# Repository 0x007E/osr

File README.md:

# `OSR` - Output Shift Register Development Board

The `OSR` is a board with an [HEF4094B](#additional-information) or any other compatible shift-register that meets the pin requirements. The board itself can be driven from `5` to `15V`. The board offers the possibility to shift serial signals to a parallel output clocked by buttons or an external signal from any other logic board.

| Experience  | Level                                                                               |
|:------------|:-----------------------------------------------------------------------------------:|
| Soldering   |  |

# Downloads

| Type      | File                                                                                                                                                 | Description     |
|:---------:|:----------------------------------------------------------------------------------------------------------------------------------------------------:|:----------------|
| Schematic | [pdf](https://github.com/0x007E/osr/releases/latest/download/schematic.pdf) / [cadlab](https://cadlab.io/project/30669/main/files)                   | Schematic files |
| Board     | [pdf](https://github.com/0x007E/osr/releases/latest/download/pcb.pdf) / [cadlab](https://cadlab.io/project/30669/main/files)                         | Board file      |
| Drill     | [pdf](https://github.com/0x007E/osr/releases/latest/download/drill.pdf)                                                                              | Drill file      |
| BoM | [xlsx](https://github.com/0x007E/osr/releases/latest/download/bom.xlsx) / [html](https://github.com/0x007E/osr/releases/latest/download/bom.html)          | Bill of Material as Excel/interactive HTML |
| PCB    | [zip](https://github.com/0x007E/osr/releases/latest/download/kicad.zip) / [tar](https://github.com/0x007E/osr/releases/latest/download/kicad.tar.gz)    | KiCAD/Gerber/BoM/Drill files       |
| Mechanical | [zip](https://github.com/0x007E/osr/releases/latest/download/freecad.zip) / [tar](https://github.com/0x007E/osr/releases/latest/download/freecad.tar.gz) | FreeCAD/Housing and PCB (STEP/STL) files     |

# Hardware

The pcb is created with `KiCAD`. All files are built with `github actions` so that they are ready for a production environment.

## PCB

The circuit board is populated on both sides (Top, Bottom). The best way for soldering the `SMD` components is within a vapor phase soldering system and for the `THT` components with a standard soldering system.

### Top Layer

### Bottom Layer

# Additional Information

| Type       | Link                                                                 | Description                      |
|:----------:|:--------------------------------------------------------------------:|:---------------------------------|
| HEF4094B   | [pdf](https://assets.nexperia.com/documents/data-sheet/HEF4094B.pdf) | 8-stage shift-and-store register |

---

R. GAECHTER

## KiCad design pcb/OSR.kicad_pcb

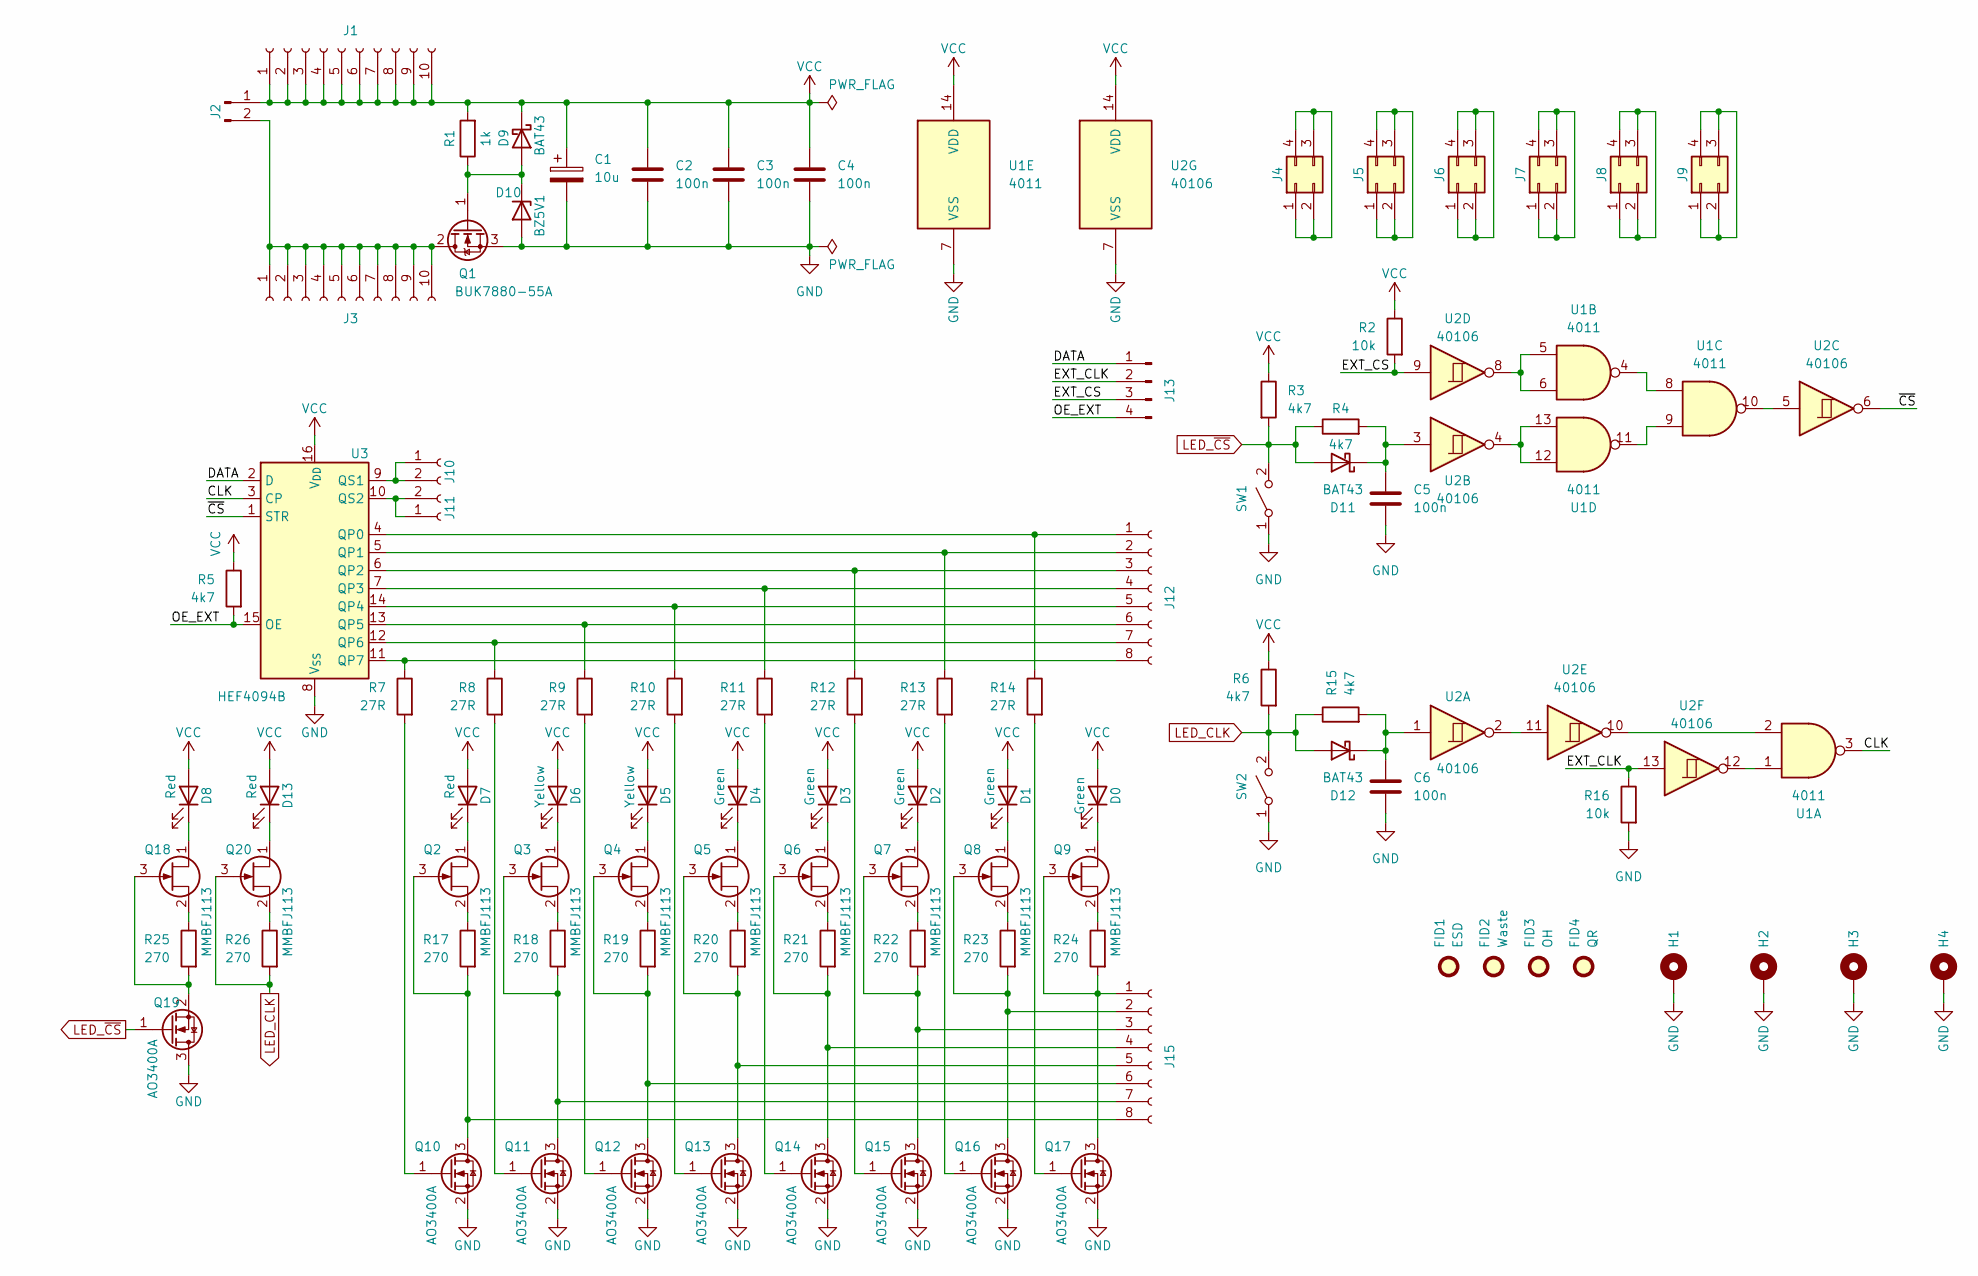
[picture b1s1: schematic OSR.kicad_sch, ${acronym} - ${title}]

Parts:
C1: 10u; CP_Radial_D6.3mm_P2.50mm
C2, C3, C4, C5, C6: 100n; C_1206_3216Metric
D0, D1, D2, D3, D4: Green; LED_1206_3216Metric
D5, D6: Yellow; LED_1206_3216Metric
D7, D8, D13: Red; LED_1206_3216Metric
D9, D11, D12: BAT43; D_MiniMELF
D10: BZ5V1; D_MiniMELF
FID1: ESD; ESD-Logo_6.6x6mm_SilkScreen
FID2: Waste; WEEE-Logo_4.2x6mm_SilkScreen
FID3: OH; OSHW-Logo_5.7x6mm_SilkScreen
FID4: QR; QR_0x007e
H1, H2, H3, H4: MountingHole_Pad; MountingHole_3.2mm_M3_Pad
J1, J3: Conn_01x10_Socket; PinSocket_1x10_P2.54mm_Vertical; DigiKey 2057-RS1-10-G-ND
J2: Conn_01x02_Pin; PinHeader_1x02_P2.54mm_Vertical
J4, J5, J6, J7, J8, J9: Conn_02x02_Counter_Clockwise; PinSocket_2x02_P2.54mm_Vertical; DigiKey 2057-RS2-04-G-ND
J10, J11: Conn_01x02_Socket; PinSocket_1x02_P2.54mm_Vertical; DigiKey 2057-RS1-02-G-ND
J12, J15: Conn_01x08_Socket; PinSocket_1x08_P2.54mm_Vertical; DigiKey 2057-RS1-08-G-ND
J13: Conn_01x04_Pin; PinHeader_1x04_P2.54mm_Vertical
Q1: BUK7880-55A; SOT-223-3_TabPin2
Q2, Q3, Q4, Q5, Q6, Q7, Q8, Q9, Q18, Q20: MMBFJ113; SOT-23; DigiKey MMBFJ113CT-ND
Q10, Q11, Q12, Q13, Q14, Q15, Q16, Q17, Q19: AO3400A; SOT-23-3
R1: 1k; R_1206_3216Metric
R2, R16: 10k; R_1206_3216Metric
R3, R4, R5, R6, R15: 4k7; R_1206_3216Metric
R7, R8, R9, R10, R11, R12, R13, R14: 27R; R_1206_3216Metric
R17, R18, R19, R20, R21, R22, R23, R24, R25, R26: 270; R_1206_3216Metric
SW1, SW2: SW_SPST; SW_SPST_PTS645
U1: 4011; SOIC-14_3.9x8.7mm_P1.27mm
U2: 40106; SOIC-14_3.9x8.7mm_P1.27mm; DigiKey 296-14081-1-ND
U3: HEF4094B; SOIC-16_3.9x9.9mm_P1.27mm; DigiKey 1727-3062-1-ND

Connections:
/CLK: U1.3, U3.3 (CP)
/DATA: J13.1, U3.2 (D)
/EXT_CLK: J13.2, R16.1, U2.13
/EXT_CS: J13.3, R2.2, U2.9
/OE_EXT: J13.4, R5.2, U3.15 (OE)
/~CS: U2.6, U3.1 (STR)
GND: C1.2, C2.2, C3.2, C4.2, C5.2, C6.2, D10.2 (A), H1.1, H2.1, H3.1, H4.1, Q1.3 (S), Q10.2 (S), Q11.2 (S), Q12.2 (S), Q13.2 (S), Q14.2 (S), Q15.2 (S), Q16.2 (S), Q17.2 (S), Q19.3 (D), R16.2, SW1.1 (A), SW2.1 (A), U1.7 (VSS), U2.7 (VSS), U3.8 (V_{SS})
LED_CLK: D12.2 (A), Q20.3 (G), R6.2, R15.1, R26.2, SW2.2 (B)
LED_~CS: D11.2 (A), Q19.1 (G), R3.2, R4.1, SW1.2 (B)
unnamed: D0.1 (K), Q9.1 (D)
unnamed: D1.1 (K), Q8.1 (D)
unnamed: D2.1 (K), Q7.1 (D)
unnamed: D3.1 (K), Q6.1 (D)
unnamed: D4.1 (K), Q5.1 (D)
unnamed: D5.1 (K), Q4.1 (D)
unnamed: D6.1 (K), Q3.1 (D)
unnamed: D7.1 (K), Q2.1 (D)
unnamed: D8.1 (K), Q18.1 (D)
unnamed: D9.2 (A), D10.1 (K), Q1.1 (G), R1.1
unnamed: C5.1, D11.1 (K), R4.2, U2.3
unnamed: C6.1, D12.1 (K), R15.2, U2.1
unnamed: D13.1 (K), Q20.1 (D)
unnamed: J2.2, J3.1, J3.2, J3.3, J3.4, J3.5, J3.6, J3.7, J3.8, J3.9, J3.10, Q1.2 (D)
unnamed: J4.1, J4.2, J4.3, J4.4
unnamed: J5.1, J5.2, J5.3, J5.4
unnamed: J6.1, J6.2, J6.3, J6.4
unnamed: J7.1, J7.2, J7.3, J7.4
unnamed: J8.1, J8.2, J8.3, J8.4
unnamed: J9.1, J9.2, J9.3, J9.4
unnamed: J10.1, J10.2, U3.9 (QS1)
unnamed: J11.1, J11.2, U3.10 (QS2)
unnamed: J12.1, R14.1, U3.4 (QP0)
unnamed: J12.2, R13.1, U3.5 (QP1)
unnamed: J12.3, R12.1, U3.6 (QP2)
unnamed: J12.4, R11.1, U3.7 (QP3)
unnamed: J12.5, R10.1, U3.14 (QP4)
unnamed: J12.6, R9.1, U3.13 (QP5)
unnamed: J12.7, R8.1, U3.12 (QP6)
unnamed: J12.8, R7.1, U3.11 (QP7)
unnamed: J15.1, Q9.3 (G), Q17.3 (D), R24.2
unnamed: J15.2, Q8.3 (G), Q16.3 (D), R23.2
unnamed: J15.3, Q7.3 (G), Q15.3 (D), R22.2
unnamed: J15.4, Q6.3 (G), Q14.3 (D), R21.2
unnamed: J15.5, Q5.3 (G), Q13.3 (D), R20.2
unnamed: J15.6, Q4.3 (G), Q12.3 (D), R19.2
unnamed: J15.7, Q3.3 (G), Q11.3 (D), R18.2
unnamed: J15.8, Q2.3 (G), Q10.3 (D), R17.2
unnamed: Q2.2 (S), R17.1
unnamed: Q3.2 (S), R18.1
unnamed: Q4.2 (S), R19.1
unnamed: Q5.2 (S), R20.1
unnamed: Q6.2 (S), R21.1
unnamed: Q7.2 (S), R22.1
unnamed: Q8.2 (S), R23.1
unnamed: Q9.2 (S), R24.1
unnamed: Q10.1 (G), R7.2
unnamed: Q11.1 (G), R8.2
unnamed: Q12.1 (G), R9.2
unnamed: Q13.1 (G), R10.2
unnamed: Q14.1 (G), R11.2
unnamed: Q15.1 (G), R12.2
unnamed: Q16.1 (G), R13.2
unnamed: Q17.1 (G), R14.2
unnamed: Q18.3 (G), Q19.2 (S), R25.2
unnamed: Q18.2 (S), R25.1
unnamed: Q20.2 (S), R26.1
unnamed: U1.1, U2.12
unnamed: U1.2, U2.10
unnamed: U1.4, U1.8
unnamed: U1.5, U1.6, U2.8
unnamed: U1.10, U2.5
unnamed: U1.9, U1.11
unnamed: U1.12, U1.13, U2.4
unnamed: U2.2, U2.11
VCC: C1.1, C2.1, C3.1, C4.1, D0.2 (A), D1.2 (A), D2.2 (A), D3.2 (A), D4.2 (A), D5.2 (A), D6.2 (A), D7.2 (A), D8.2 (A), D9.1 (K), D13.2 (A), J1.1, J1.2, J1.3, J1.4, J1.5, J1.6, J1.7, J1.8, J1.9, J1.10, J2.1, R1.2, R2.1, R3.1, R5.1, R6.1, U1.14 (VDD), U2.14 (VDD), U3.16 (V_{DD})

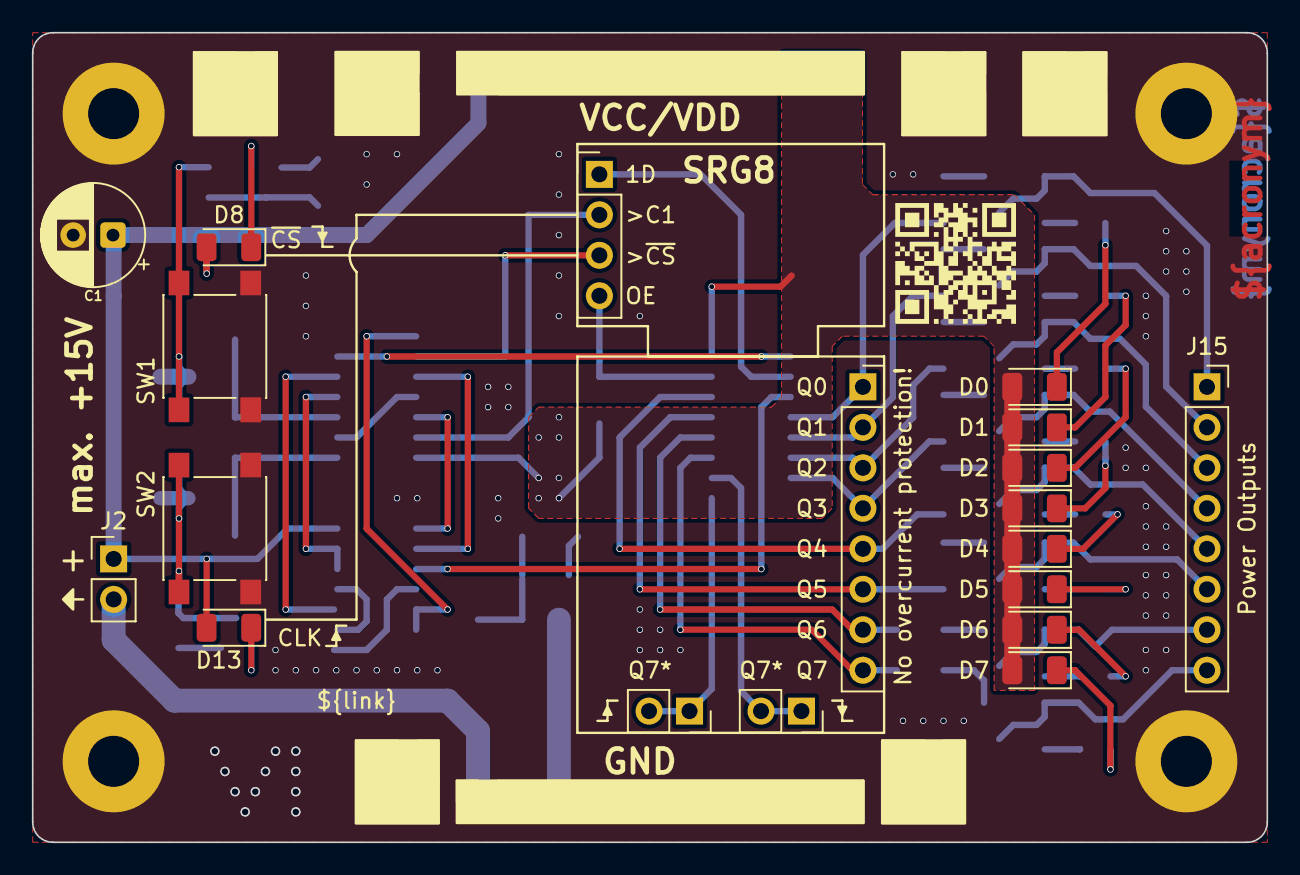
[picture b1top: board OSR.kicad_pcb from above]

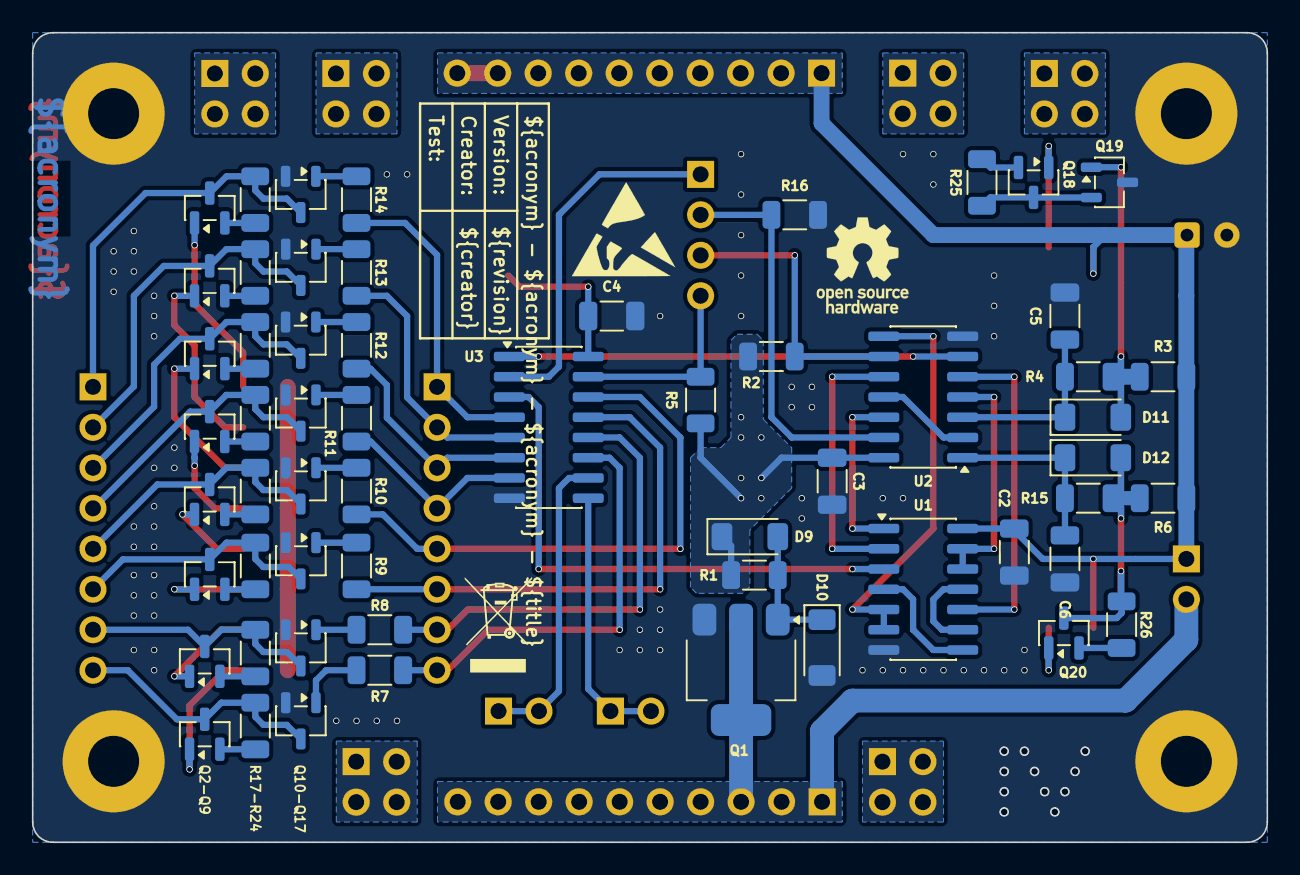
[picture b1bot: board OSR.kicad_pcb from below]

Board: 2 copper layers, 77.5 x 50.8 mm, 93 parts (61 on the bottom side), 75 nets.

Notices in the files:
README.md:
License CC By-NC-SA
parts and their libraries:
license: CC BY-NC-SA 4.0
